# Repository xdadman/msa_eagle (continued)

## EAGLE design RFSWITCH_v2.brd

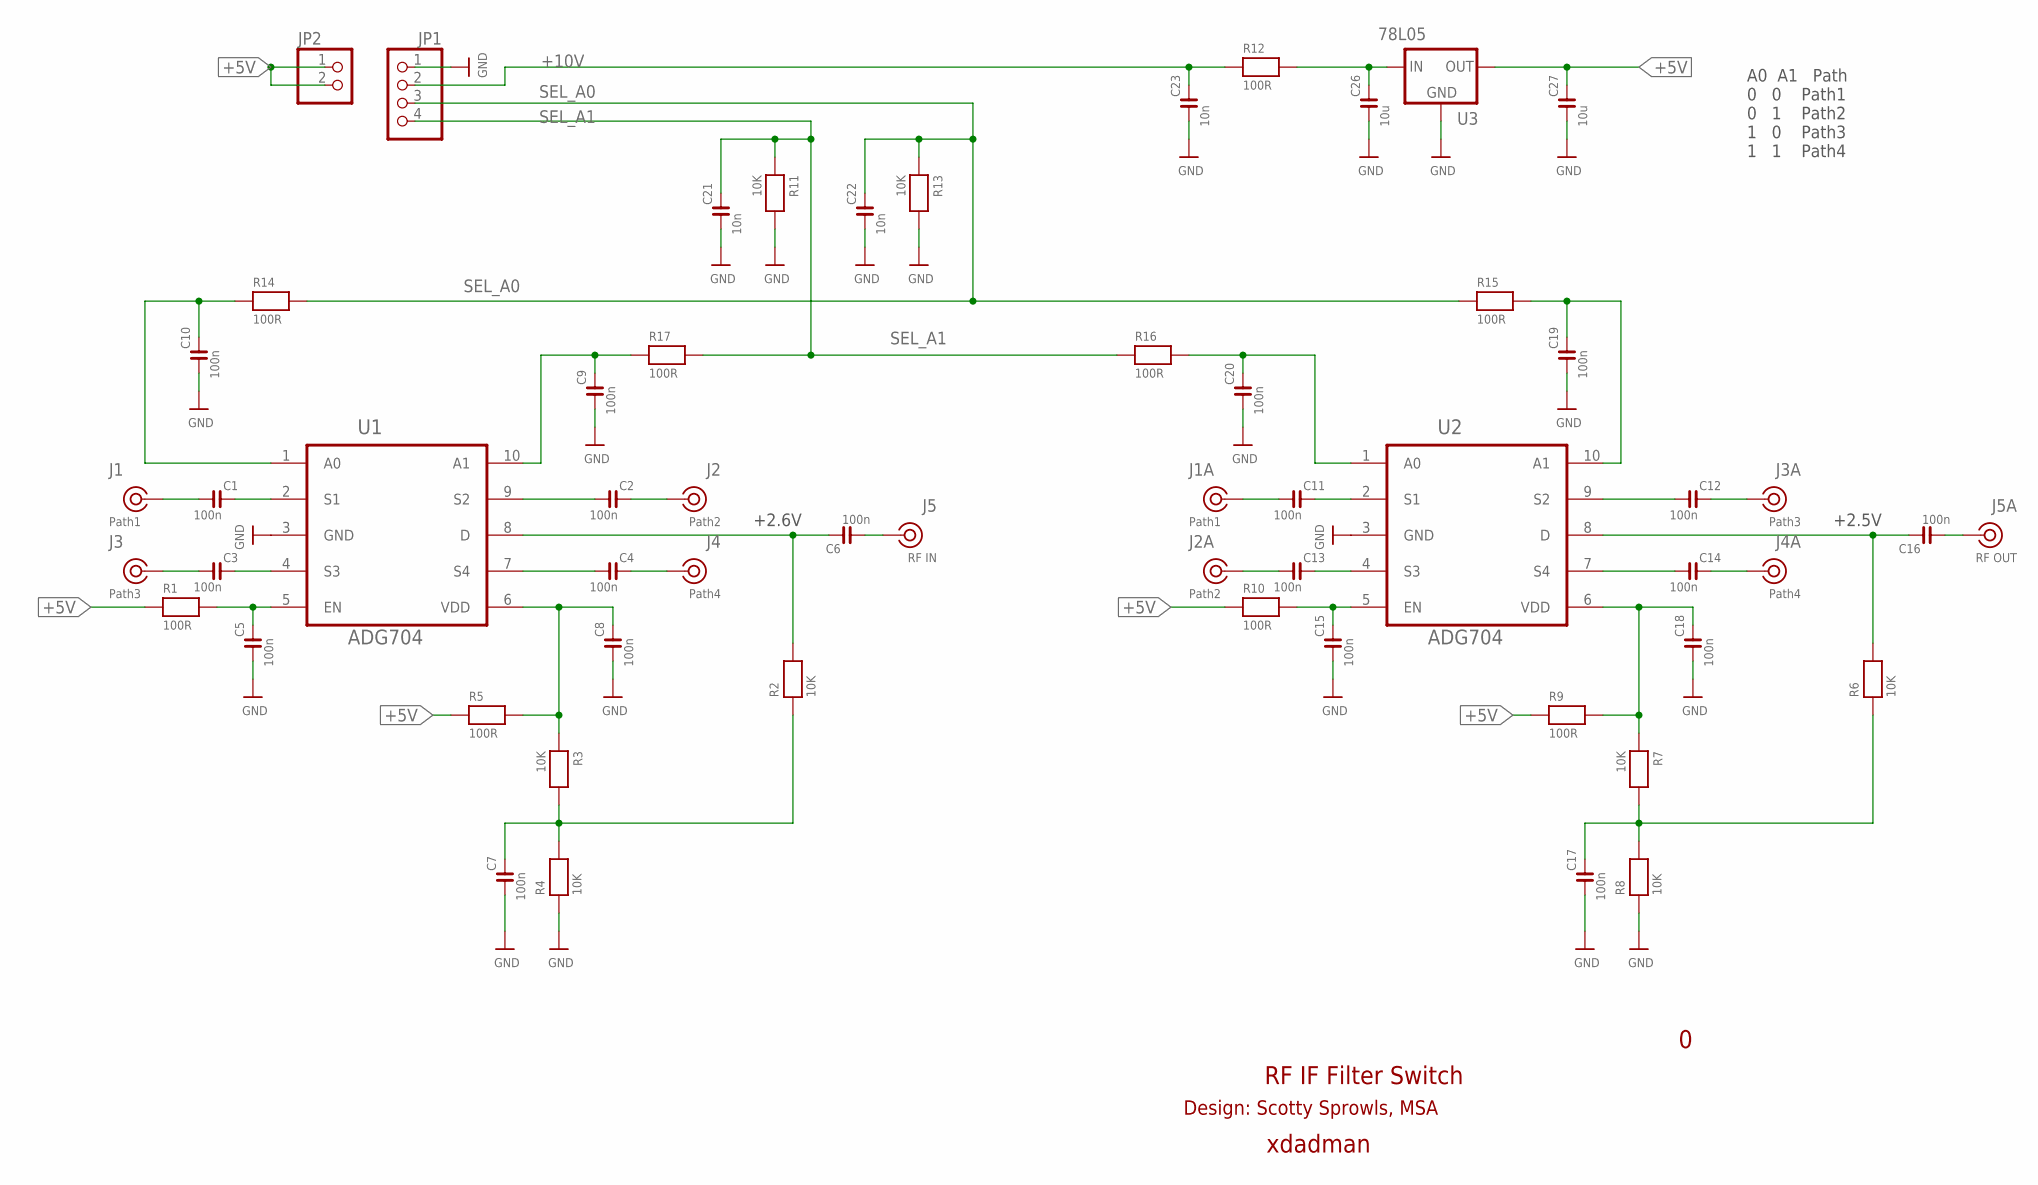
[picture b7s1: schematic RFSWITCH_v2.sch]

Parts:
C1, C2, C3, C4, C6, C7, C9, C10, C11, C12, C13, C14, C16, C17, C19, C20: 100n; C0805
C5, C8, C15, C18: 100n; C0603
C21, C22, C23: 10n; C0805
C26, C27: 10u; C1206
J1, J1A: Path1; SLIM_COAX_PAD
J2, J2A: Path2; SLIM_COAX_PAD
J3, J3A: Path3; SLIM_COAX_PAD
J4, J4A: Path4; SLIM_COAX_PAD
J5: RF IN; SLIM_COAX_PAD
J5A: RF OUT; SLIM_COAX_PAD
JP1: PINHD-1X4; 1X04
JP2: PINHD-1X2; 1X02
R1, R5, R9, R10, R12, R14, R15, R16, R17: 100R; C0805
R2, R3, R4, R6, R7, R8, R11, R13: 10K; R0805
U1, U2: ADG704; SOP50P490X110-10N-ADG704
U3: 78L05; SOT89

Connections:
+5V: C27.2, JP2.1, JP2.2, R1.1, R5.1, R9.1, R10.1, U3.1 (OUT)
+10V: C23.2, JP1.2, R12.1
GND: C5.1, C7.1, C8.1, C9.1, C10.1, C15.1, C17.1, C18.1, C19.1, C20.1, C21.1, C22.1, C23.1, C26.1, C27.1, J1.GND, J1A.GND, J2.GND, J2A.GND, J3.GND, J3A.GND, J4.GND, J4A.GND, J5.GND, J5A.GND, JP1.1, R4.1, R8.1, R11.2, R13.2, U1.3 (GND), U2.3 (GND), U3.2 (GND), U3.4 (GND)
IN: C6.2, R2.2, U1.8 (D)
IN1: C16.2, R6.2, U2.8 (D)
unnamed: C1.2, U1.2 (S1)
unnamed: C1.1, J1.SIG (1)
unnamed: C3.2, U1.4 (S3)
unnamed: C4.1, U1.7 (S4)
unnamed: C2.1, U1.9 (S2)
unnamed: C2.2, J2.SIG (1)
unnamed: C4.2, J4.SIG (1)
unnamed: C3.1, J3.SIG (1)
unnamed: C6.1, J5.SIG (1)
unnamed: C8.2, R3.1, R5.2, U1.6 (VDD)
unnamed: C7.2, R2.1, R3.2, R4.2
unnamed: C11.2, U2.2 (S1)
unnamed: C11.1, J1A.SIG (1)
unnamed: C13.2, U2.4 (S3)
unnamed: C14.1, U2.7 (S4)
unnamed: C12.1, U2.9 (S2)
unnamed: C12.2, J3A.SIG (1)
unnamed: C14.2, J4A.SIG (1)
unnamed: C13.1, J2A.SIG (1)
unnamed: C16.1, J5A.SIG (1)
unnamed: C17.2, R6.1, R7.2, R8.2
unnamed: C18.2, R7.1, R9.2, U2.6 (VDD)
unnamed: C15.2, R10.2, U2.5 (EN)
unnamed: C5.2, R1.2, U1.5 (EN)
unnamed: C26.2, R12.2, U3.3 (IN)
unnamed: C10.2, R14.1, U1.1 (A0)
unnamed: C9.2, R17.1, U1.10 (A1)
unnamed: C20.2, R16.2, U2.1 (A0)
unnamed: C19.2, R15.2, U2.10 (A1)
SEL_A0: C22.2, JP1.3, R13.1, R14.2, R15.1
SEL_A1: C21.2, JP1.4, R11.1, R16.1, R17.2

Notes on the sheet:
+2.6V
+2.5V
A0 A1 Path 0 0 Path1 0 1 Path2 1 0 Path3 1 1 Path4
xdadman
RF IF Filter Switch
Design: Scotty Sprowls, MSA

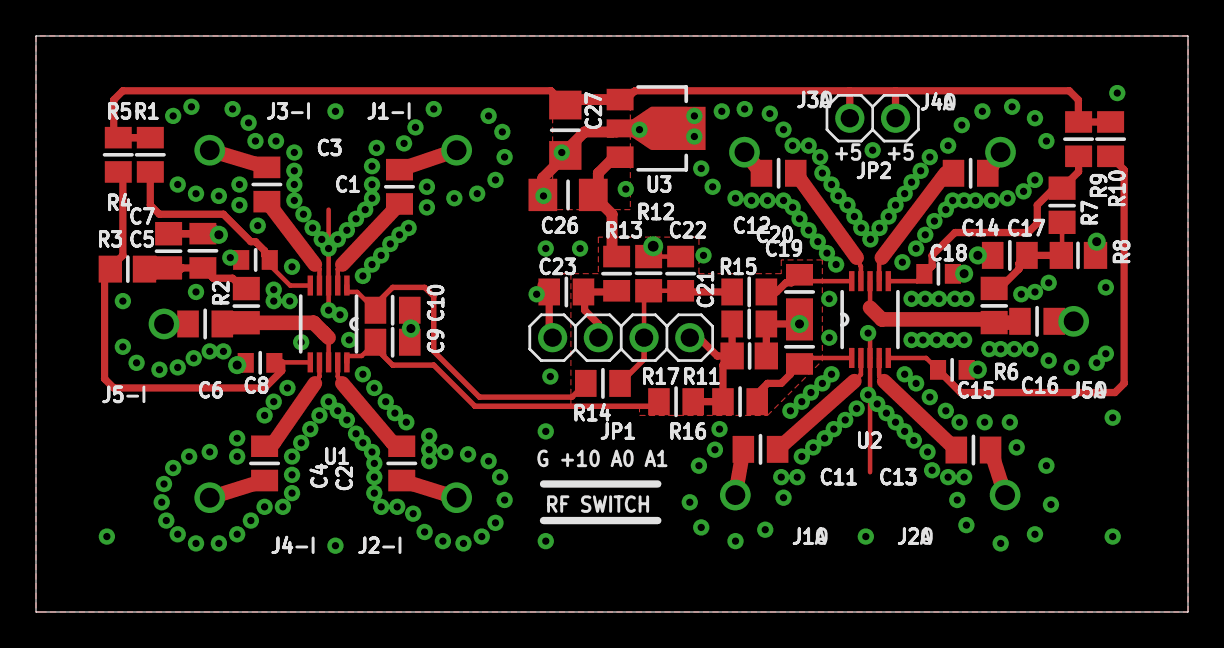
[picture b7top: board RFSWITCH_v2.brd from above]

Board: 2 copper layers, 64.0 x 32.0 mm, 57 parts (0 on the bottom side), 36 nets.
